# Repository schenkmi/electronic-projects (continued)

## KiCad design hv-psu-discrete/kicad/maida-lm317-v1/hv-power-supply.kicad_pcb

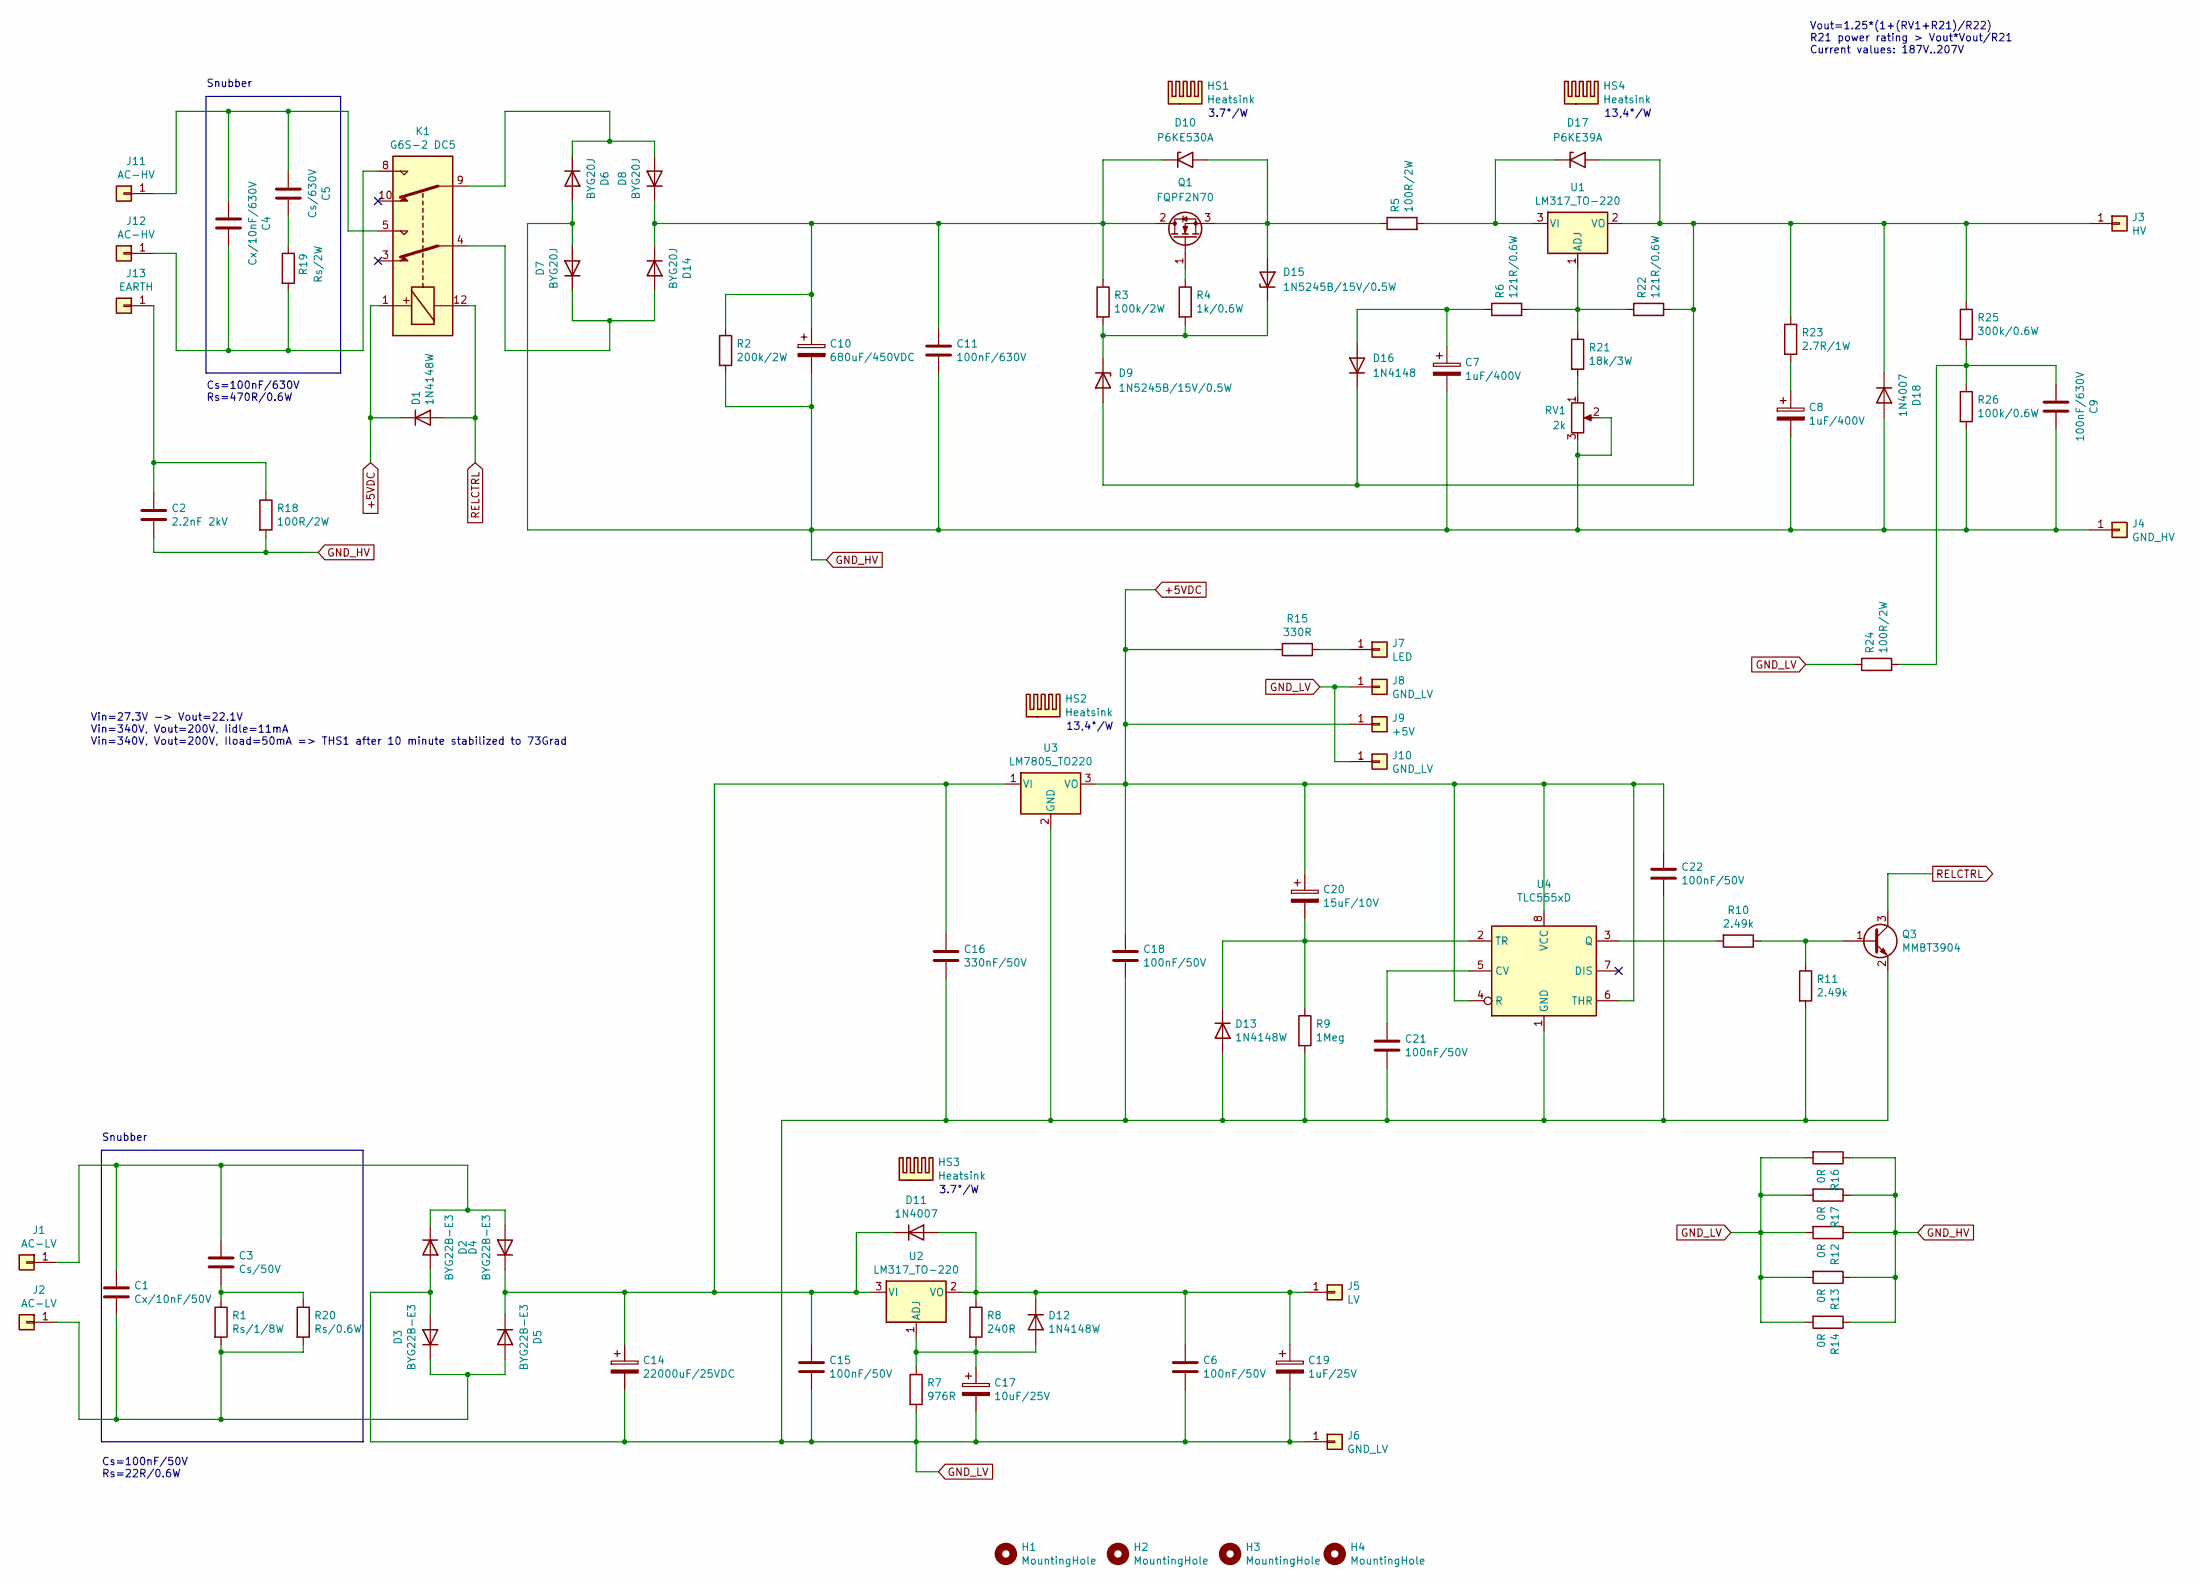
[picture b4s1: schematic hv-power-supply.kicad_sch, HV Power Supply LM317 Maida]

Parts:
C1: Cx/10nF/50V; C_0805_2012Metric_Pad1.18x1.45mm_HandSolder
C2: 2.2nF 2kV; C_Rect_L18.0mm_W5.0mm_P15.00mm_FKS3_FKP3
C3: Cs/50V; C_0805_2012Metric_Pad1.18x1.45mm_HandSolder
C4: Cx/10nF/630V; C_Rect_L13.0mm_W4.0mm_P10.00mm_FKS3_FKP3_MKS4
C5: Cs/630V; C_Rect_L18.0mm_W5.0mm_P15.00mm_FKS3_FKP3
C6, C15, C18, C21, C22: 100nF/50V; C_0805_2012Metric_Pad1.18x1.45mm_HandSolder
C7, C8: 1uF/400V; CP_Radial_D6.3mm_P2.50mm
C9, C11: 100nF/630V; C_Rect_L18.0mm_W5.0mm_P15.00mm_FKS3_FKP3
C10: 680uF/450VDC; CP_Radial_D35.0mm_P10.00mm_SnapIn
C14: 22000uF/25VDC; CP_Radial_D35.0mm_P10.00mm_SnapIn
C16: 330nF/50V; C_0805_2012Metric_Pad1.18x1.45mm_HandSolder
C17: 10uF/25V; CP_Radial_D5.0mm_P2.00mm
C19: 1uF/25V; CP_Radial_D5.0mm_P2.00mm
C20: 15uF/10V; CP_EIA-3216-12_Kemet-S_Pad1.58x1.35mm_HandSolder
D1, D12, D13: 1N4148W; D_SOD-123
D2, D3, D4, D5: BYG22B-E3; D_SMA_Handsoldering
D6, D7, D8, D14: BYG20J; D_SMA_Handsoldering
D9, D15: 1N5245B/15V/0.5W; D_DO-35_SOD27_P7.62mm_Horizontal
D10: P6KE530A; D_DO-15_P12.70mm_Horizontal
D11: 1N4007; D_SMA_Handsoldering
D16: 1N4148; D_DO-35_SOD27_P7.62mm_Horizontal
D17: P6KE39A; D_DO-15_P12.70mm_Horizontal
D18: 1N4007; D_DO-41_SOD81_P10.16mm_Horizontal
H1, H2, H3, H4: MountingHole; MountingHole_3.2mm_M3
HS1, HS3: Heatsink; Heatsink_Fischer_SK129-STS_42x25mm_2xDrill2.5mm
HS2, HS4: Heatsink; Heatsink_Fischer_SK104-STC-STIC_35x13mm_2xDrill2.5mm
J1, J2: AC-LV; Pin_D1.3mm_L11.0mm
J3: HV; Pin_D1.3mm_L11.0mm
J4: GND_HV; Pin_D1.3mm_L11.0mm
J5: LV; Pin_D1.3mm_L11.0mm
J6: GND_LV; Pin_D1.3mm_L11.0mm
J7: LED; Pin_D1.0mm_L10.0mm
J8, J10: GND_LV; Pin_D1.0mm_L10.0mm
J9: +5V; Pin_D1.0mm_L10.0mm
J11, J12: AC-HV; Pin_D1.3mm_L11.0mm
J13: EARTH; Pin_D1.3mm_L11.0mm
K1: G6S-2 DC5; Relay_DPDT_Omron_G6S-2
Q1: FQPF2N70; TO-220-3_Vertical
Q3: MMBT3904; SOT-23
R1: Rs/1/8W; R_0805_2012Metric_Pad1.20x1.40mm_HandSolder
R2: 200k/2W; R_Axial_DIN0414_L11.9mm_D4.5mm_P15.24mm_Horizontal
R3: 100k/2W; R_Axial_DIN0414_L11.9mm_D4.5mm_P15.24mm_Horizontal
R4: 1k/0.6W; R_Axial_DIN0207_L6.3mm_D2.5mm_P10.16mm_Horizontal
R5, R18, R24: 100R/2W; R_Axial_DIN0414_L11.9mm_D4.5mm_P15.24mm_Horizontal
R6, R22: 121R/0.6W; R_Axial_DIN0207_L6.3mm_D2.5mm_P10.16mm_Horizontal
R7: 976R; R_0805_2012Metric_Pad1.20x1.40mm_HandSolder
R8: 240R; R_0805_2012Metric_Pad1.20x1.40mm_HandSolder
R9: 1Meg; R_0805_2012Metric_Pad1.20x1.40mm_HandSolder
R10, R11: 2.49k; R_0805_2012Metric_Pad1.20x1.40mm_HandSolder
R12, R13, R14, R16, R17: 0R; R_1206_3216Metric_Pad1.30x1.75mm_HandSolder
R15: 330R; R_0805_2012Metric_Pad1.20x1.40mm_HandSolder
R19: Rs/2W; R_Axial_DIN0414_L11.9mm_D4.5mm_P15.24mm_Horizontal
R20: Rs/0.6W; R_Axial_DIN0207_L6.3mm_D2.5mm_P10.16mm_Horizontal
R21: 18k/3W; R_Axial_DIN0614_L14.3mm_D5.7mm_P20.32mm_Horizontal
R23: 2.7R/1W; R_Axial_DIN0207_L6.3mm_D2.5mm_P10.16mm_Horizontal
R25: 300k/0.6W; R_Axial_DIN0207_L6.3mm_D2.5mm_P10.16mm_Horizontal
R26: 100k/0.6W; R_Axial_DIN0207_L6.3mm_D2.5mm_P10.16mm_Horizontal
RV1: 2k; Potentiometer_Bourns_3296W_Vertical
U1, U2: LM317_TO-220; TO-220-3_Vertical
U3: LM7805_TO220; TO-220-3_Vertical
U4: TLC555xD; SOIC-8_3.9x4.9mm_P1.27mm

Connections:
+5VDC: C18.1, C20.1, C22.1, D1.1 (K), J9.1, K1.1, R15.2, U3.3 (VO), U4.4 (R), U4.6 (THR), U4.8 (VCC)
GND_HV: C2.2, C7.2, C8.2, C9.1, C10.2, C11.2, D6.2 (A), D7.2 (A), D18.2 (A), J4.1, R2.2, R12.1, R13.1, R14.1, R16.1, R17.1, R18.2, R26.2, RV1.2, RV1.3
GND_LV: C6.2, C14.2, C15.2, C16.2, C17.2, C18.2, C19.2, C21.2, C22.2, D2.2 (A), D3.2 (A), D13.2 (A), J6.1, J8.1, J10.1, Q3.2 (E), R7.2, R9.2, R11.2, R12.2, R13.2, R14.2, R16.2, R17.2, R24.1, U3.2 (GND), U4.1 (GND)
unnamed: C1.1, C3.1, D2.1 (K), D4.2 (A), J1.1
unnamed: C1.2, D3.1 (K), D5.2 (A), J2.1, R1.2, R20.2
unnamed: C2.1, J13.1, R18.1
unnamed: C3.2, R1.1, R20.1
unnamed: C4.1, J12.1, K1.8, R19.2
unnamed: C4.2, C5.2, J11.1, K1.5
unnamed: C5.1, R19.1
unnamed: C7.1, D16.2 (A), R6.1
unnamed: C8.1, R23.2
unnamed: C9.2, R24.2, R25.2, R26.1
unnamed: C10.1, C11.1, D8.1 (K), D10.1 (A1), D14.1 (K), Q1.2 (D), R2.1, R3.1
unnamed: C14.1, C15.1, C16.1, D4.1 (K), D5.1 (K), D11.1 (K), U2.3 (VI), U3.1 (VI)
unnamed: C17.1, D12.2 (A), R7.1, R8.2, U2.1 (ADJ)
unnamed: C6.1, C19.1, D11.2 (A), D12.1 (K), J5.1, R8.1, U2.2 (VO)
unnamed: C20.2, D13.1 (K), R9.1, U4.2 (TR)
unnamed: C21.1, U4.5 (CV)
unnamed: D6.1 (K), D8.2 (A), K1.9
unnamed: D10.2 (A2), D15.2 (A), Q1.3 (S), R5.1
unnamed: D7.1 (K), D14.2 (A), K1.4
unnamed: D9.1 (K), D15.1 (K), R3.2, R4.2
unnamed: D9.2 (A), D16.1 (K), D17.2 (A2), D18.1 (K), J3.1, R22.2, R23.1, R25.1, U1.2 (VO)
unnamed: D17.1 (A1), R5.2, U1.3 (VI)
unnamed: J7.1, R15.1
unnamed: Q1.1 (G), R4.1
unnamed: Q3.1 (B), R10.1, R11.1
unnamed: R10.2, U4.3 (Q)
unnamed: R6.2, R21.1, R22.1, U1.1 (ADJ)
unnamed: R21.2, RV1.1
RELCTRL: D1.2 (A), K1.12, Q3.3 (C)

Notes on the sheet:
13,4°/W
Snubber
Cs=100nF/630V Rs=470R/0.6W
3.7°/W
Vin=27.3V -> Vout=22.1V Vin=340V, Vout=200V, Iidle=11mA Vin=340V, Vout=200V, Iload=50mA => THS1 after 10 minute stabilized to 73Grad
Vout=1.25*(1+(RV1+R21)/R22) R21 power rating > Vout*Vout/R21 Current values: 187V..207V
Cs=100nF/50V Rs=22R/0.6W

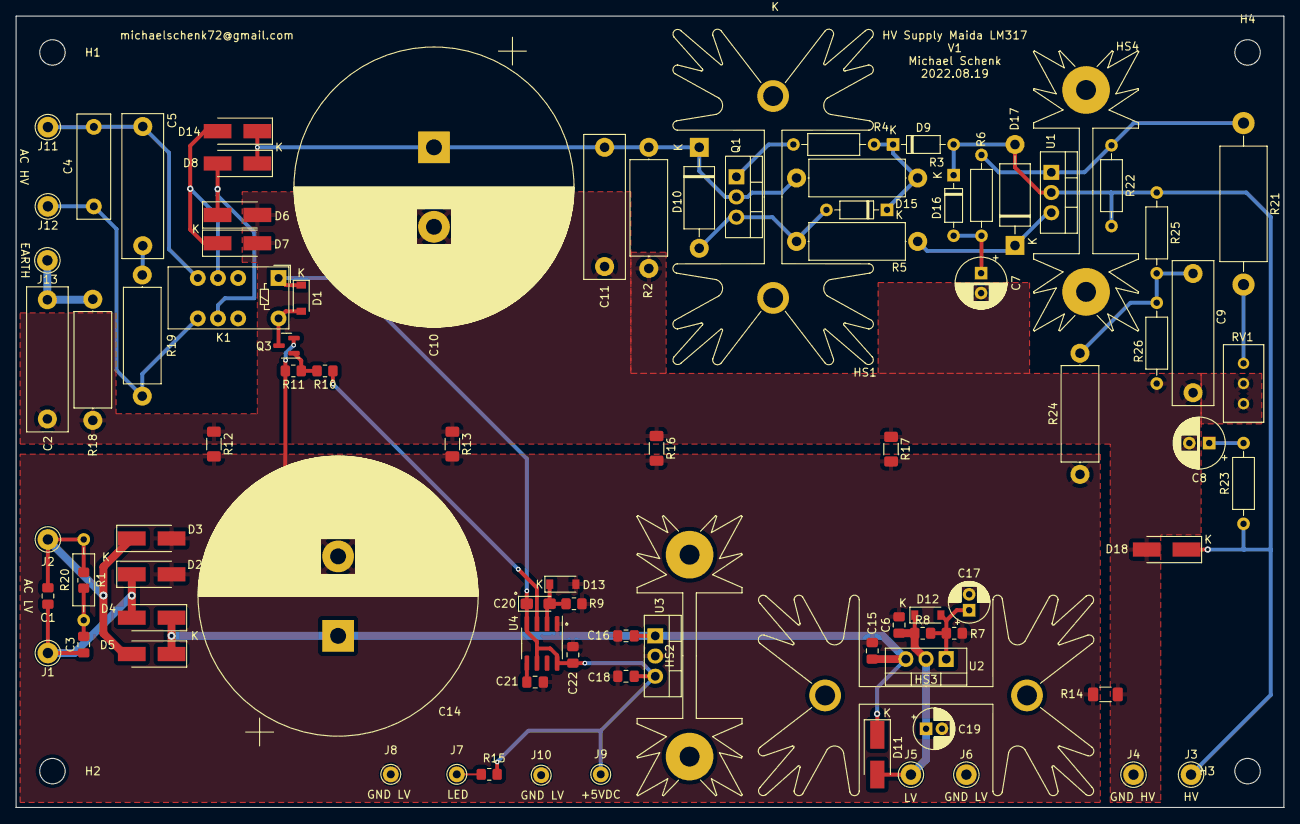
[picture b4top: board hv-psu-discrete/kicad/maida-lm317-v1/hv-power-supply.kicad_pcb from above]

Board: 2 copper layers, 159.5 x 99.6 mm, 93 parts (0 on the bottom side), 32 nets.
